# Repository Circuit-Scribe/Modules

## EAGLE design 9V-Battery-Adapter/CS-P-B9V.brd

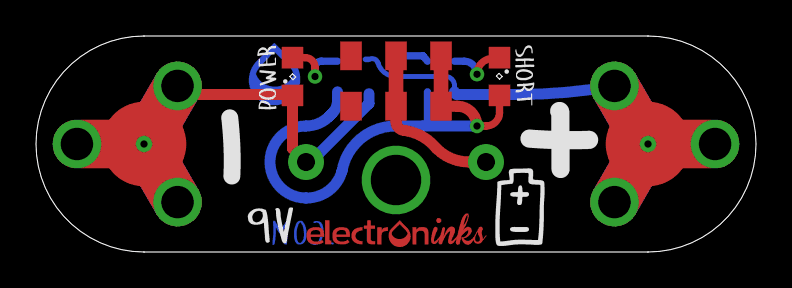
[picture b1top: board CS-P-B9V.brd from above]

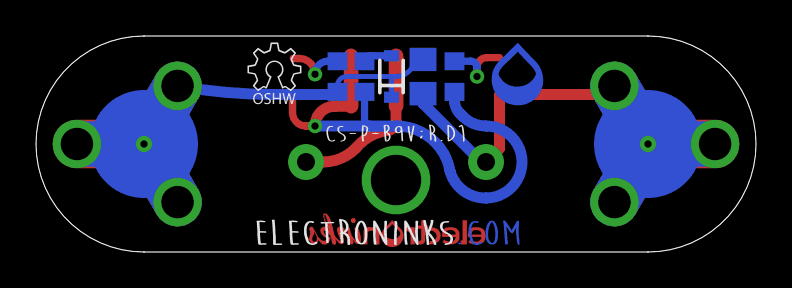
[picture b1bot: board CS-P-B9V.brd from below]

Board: 2 copper layers, 40.0 x 12.0 mm, 15 parts (9 on the bottom side), 7 nets.

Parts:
C2: 10uF; C0805
D2: DIODE Schottky 20v 0.5A b5817ws-tpmsct-nd; SOD-323
F1: PTC 0.12A 0603 507-1819-1-ND; R0603
LED1: blue; SML0805
LED2_SHORT: red; SML0805
R1: RES 500ohm 0603; R0603
R2: RES 20k 0603; R0603
U$1: 563-1340-2-ND-SWITCH
U$2, U$3: ROUND-12MM-FOOT-1.8MM; ROUND-12MM-FOOT
U$4: ELECTRONINKS_LOGO_10MM
U$5: DROPLET_LOGO_3MM
U$6: OSHW_3MM
U$7: ELECTRONINKS_COM_15MM
U$8: CS_P_B9V

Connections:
9V: U$1.P$2, U$1.P$5
GND: C2.2, LED1.C, U$2.P$1, U$2.P$2, U$2.P$3, U$2.P$4, U$2.P$5
unnamed: LED1.A, R2.1
unnamed: LED2_SHORT.C, R1.1
unnamed: D2.2, F1.2
P$20: C2.1, D2.1, R1.2, U$3.P$1, U$3.P$2, U$3.P$3, U$3.P$4, U$3.P$5
UVCC: F1.1, LED2_SHORT.A, R2.2, U$1.P$1, U$1.P$4

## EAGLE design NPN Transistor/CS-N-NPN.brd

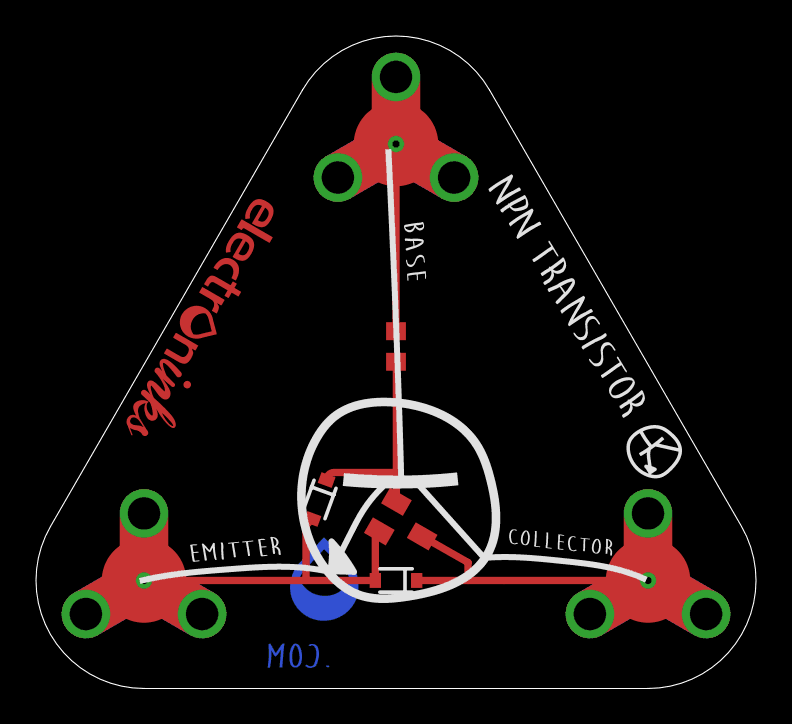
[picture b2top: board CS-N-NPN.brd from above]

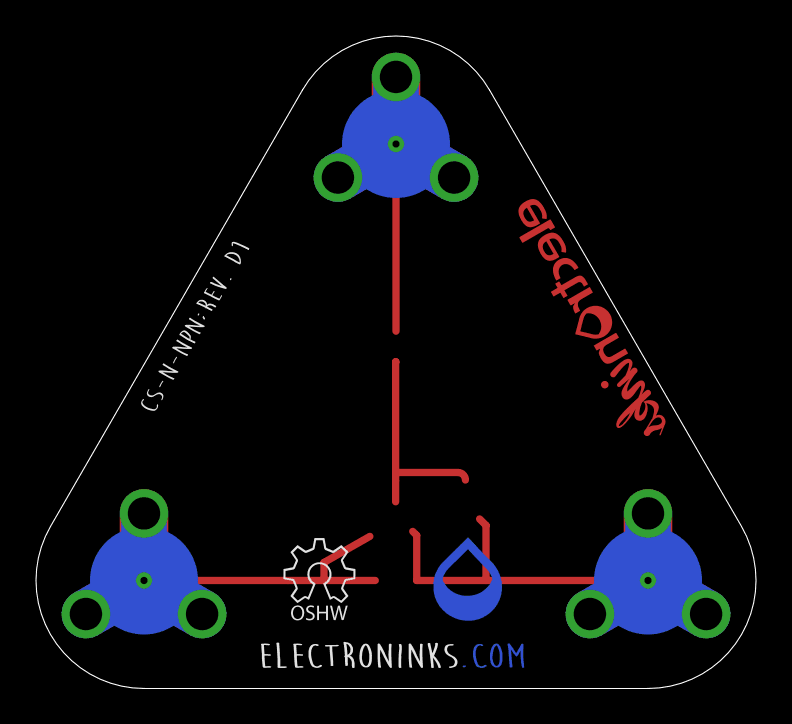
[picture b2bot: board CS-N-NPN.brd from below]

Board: 2 copper layers, 40.0 x 36.2 mm, 12 parts (4 on the bottom side), 4 nets.

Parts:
D1: Schottky 20v 0.5A b5817ws-tpmsct-nd; SOD-323
D2: Schottky 20v 0.5A b5817ws-tpmsct-nd (unused); SOD-323
R1: 1K; R0603
T1: BC846; SOT23
U$1, U$2, U$3: ROUND-12MM-FOOT-1.8MM; ROUND-12MM-FOOT
U$4: ELECTRONINKS_LOGO_15MM
U$5: DROPLET_LOGO_4MM
U$6: OSHW_4MM; OHSW_4MM
U$7: ELECTRONINKS_COM_15MM
U$8: CS_N_NPN

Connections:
unnamed: D1.1, T1.3, U$1.P$1, U$1.P$2, U$1.P$3, U$1.P$4, U$1.P$5
unnamed: D1.2, D2.2, T1.2, U$3.P$1, U$3.P$2, U$3.P$3, U$3.P$4, U$3.P$5
unnamed: D2.1, R1.2, T1.1
unnamed: R1.1, U$2.P$1, U$2.P$2, U$2.P$3, U$2.P$4, U$2.P$5
